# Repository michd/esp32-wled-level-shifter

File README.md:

# ESP32 WLED Level Shifter

A simple board to house an ESP32 dev board and a level shifter, so it can be hooked up directly to a powered 5V LED strip.

This fits a "ESP-32S Development Board", which can be found by plenty of sellers.

Designed for APA102 LEDs, so it has a CLK and DATA output.

Comes with a KiCad (6) board design and 3D-printable enclosure designed in FreeCAD.

See [Releases](https://github.com/michd/esp32-wled-level-shifter/releases) for exported PCB manufacturing files and STL files to 3D print.

## Images

The board; doesn't contain much.

Bottom section of the 3D printed box

Top section of the 3D printed box

Assembled, in real life.

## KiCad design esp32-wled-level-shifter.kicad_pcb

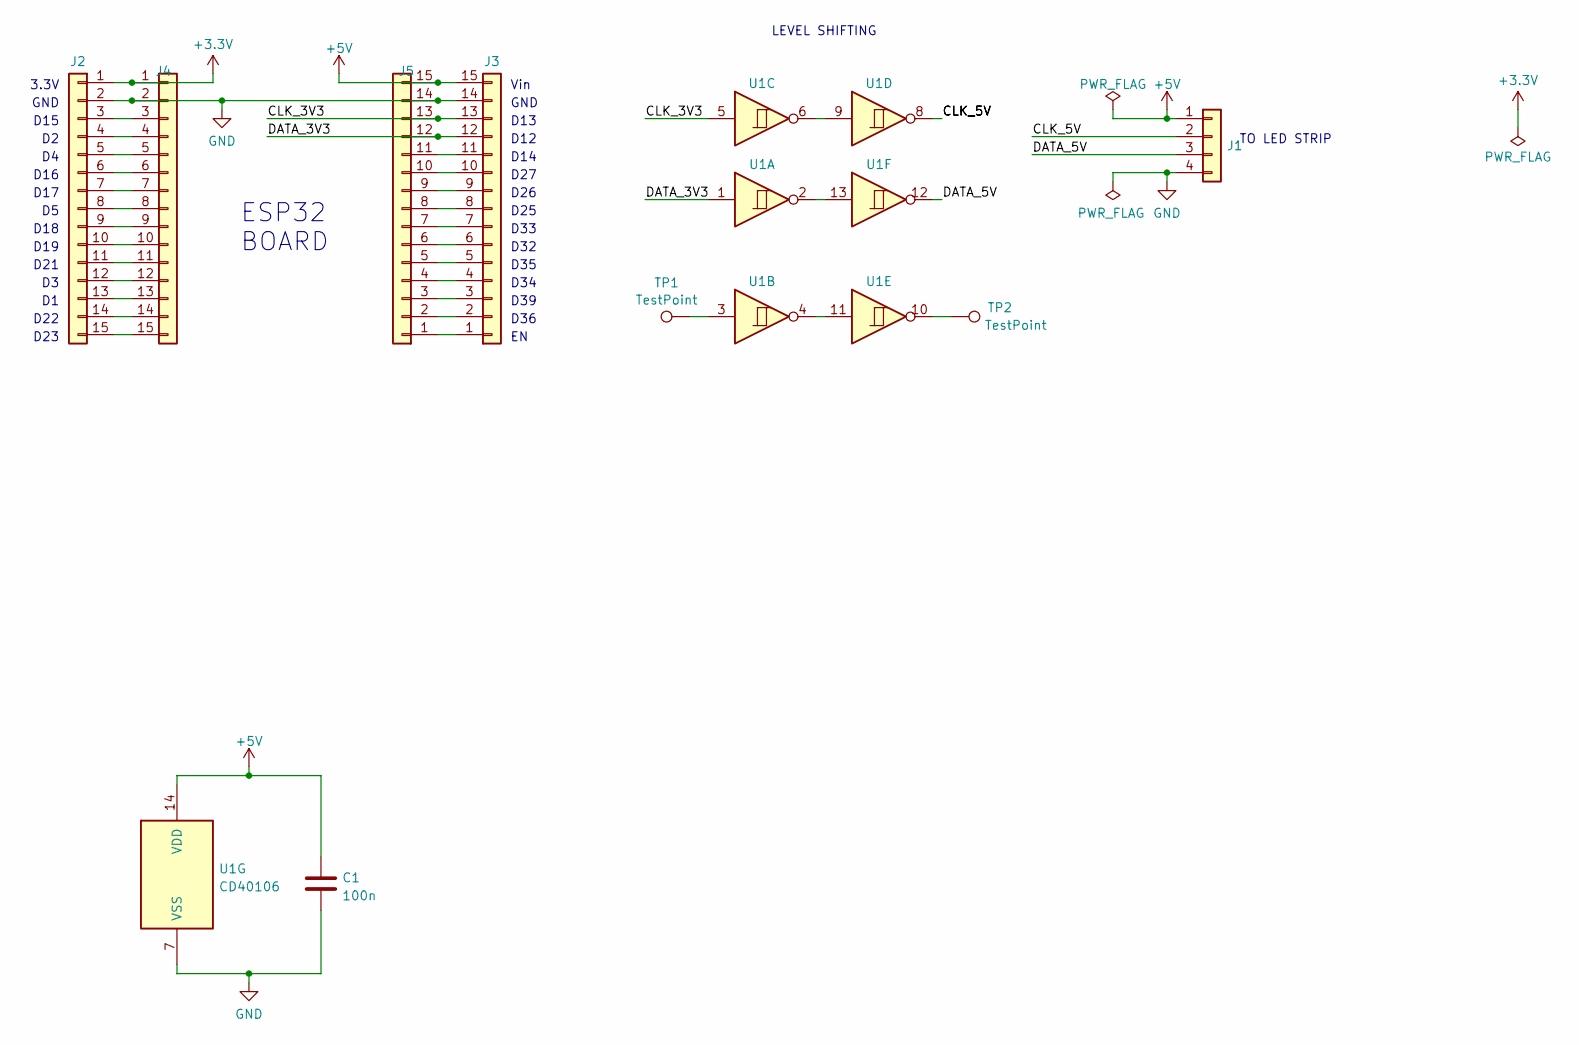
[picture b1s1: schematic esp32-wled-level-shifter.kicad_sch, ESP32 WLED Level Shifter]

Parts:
C1: 100n; C_0603_1608Metric; LCSC C14663
J1: Conn_01x04_Female; PhoenixContact_MSTBA_2,5_4-G-5,08_1x04_P5.08mm_Horizontal
J2, J3, J4, J5: Conn_01x15_Female; PinSocket_1x15_P2.54mm_Vertical
TP1, TP2: TestPoint; TestPoint_THTPad_D2.0mm_Drill1.0mm
U1: CD40106; SOIC-14_3.9x8.7mm_P1.27mm; LCSC C38184

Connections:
+3.3V: J2.1, J4.1
+5V: C1.1, J1.1, J3.15, J5.15, U1.14 (VDD)
/CLK_3V3: J3.13, J5.13, U1.5
/CLK_5V: J1.2, U1.8
/DATA_3V3: J3.12, J5.12, U1.1
/DATA_5V: J1.3, U1.12
GND: C1.2, J1.4, J2.2, J3.14, J4.2, J5.14, U1.7 (VSS)
unnamed: J2.3, J4.3
unnamed: J2.4, J4.4
unnamed: J2.5, J4.5
unnamed: J2.6, J4.6
unnamed: J2.7, J4.7
unnamed: J2.8, J4.8
unnamed: J2.9, J4.9
unnamed: J2.10, J4.10
unnamed: J2.11, J4.11
unnamed: J2.12, J4.12
unnamed: J2.13, J4.13
unnamed: J2.14, J4.14
unnamed: J2.15, J4.15
unnamed: J3.1, J5.1
unnamed: J3.2, J5.2
unnamed: J3.3, J5.3
unnamed: J3.4, J5.4
unnamed: J3.5, J5.5
unnamed: J3.6, J5.6
unnamed: J3.7, J5.7
unnamed: J3.8, J5.8
unnamed: J3.9, J5.9
unnamed: J3.10, J5.10
unnamed: J3.11, J5.11
unnamed: TP1.1, U1.3
unnamed: TP2.1, U1.10
unnamed: U1.6, U1.9
unnamed: U1.4, U1.11
unnamed: U1.2, U1.13

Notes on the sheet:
Vin
GND
D23
LEVEL SHIFTING
D14
D39
D13
D21
D34
D19
D15
D12
3.3V
D32
D25
D16
D26
D22
ESP32 BOARD
D33
D35
D17
D36
D18
TO LED STRIP
D27

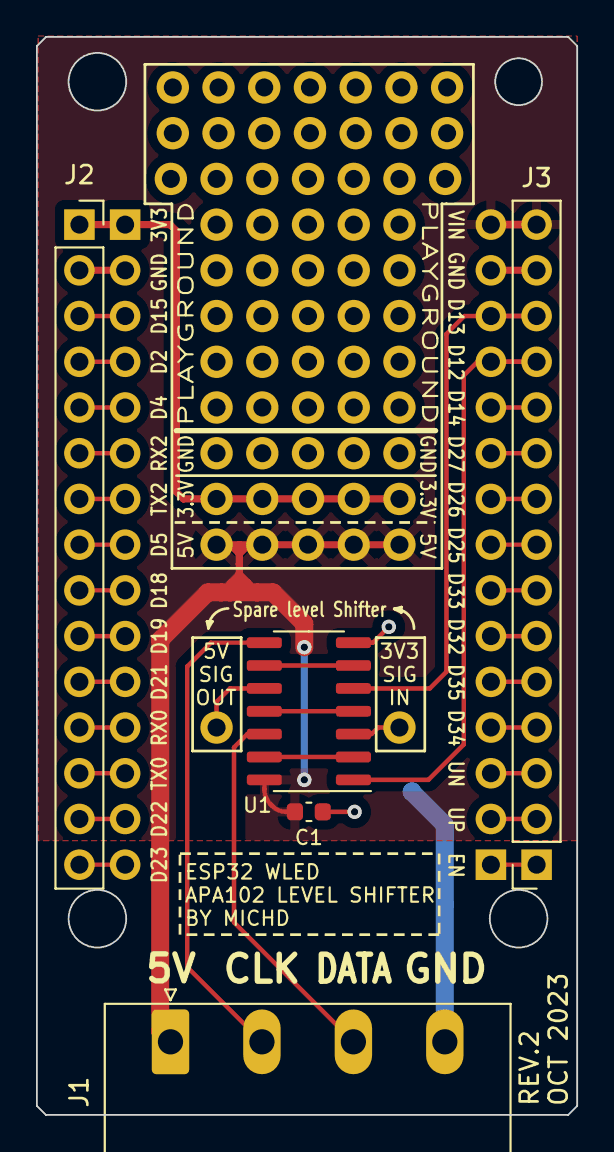
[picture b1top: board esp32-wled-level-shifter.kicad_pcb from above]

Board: 2 copper layers, 30.0 x 59.9 mm, 9 parts (0 on the bottom side), 36 nets.

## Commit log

2022-06-24 Dimension and size tweaks
    - Correctly space connectors
    - Increase size of mounting holes, allow M3
    - Chamfer board edges
    - More silkscreen markings
2022-07-08 Wip: enclosure design
2022-07-08 Finish top and bottom of enclosure, hopefully
2022-07-18 Expand README, add some images/photo
2022-08-09 Add gaps for the screw tabs in enclosure top
2023-10-08 Rev2 board with experimenting playground
